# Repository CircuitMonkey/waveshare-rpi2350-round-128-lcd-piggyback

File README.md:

# waveshare-rpi2350-round-128-lcd-piggyback
Piggyback hacking PCB for the Waveshare RPi2350/2040 round 1.28 inch 240x240 LCD

Gain solder level access to the header pins on the back of this LCB module!

These are piggyback style GPIO access connector PCBs for the Waveshare 1.28 inch round LCD with RPi2350/2040 type controller.
Amazon product link example: [https://www.amazon.com/dp/B0DM1CB4YV](https://www.amazon.com/dp/B0DM1CB4YV)

If you want to try one of these boards, simply upload the PCB KiCAD design to https://oshpark.com

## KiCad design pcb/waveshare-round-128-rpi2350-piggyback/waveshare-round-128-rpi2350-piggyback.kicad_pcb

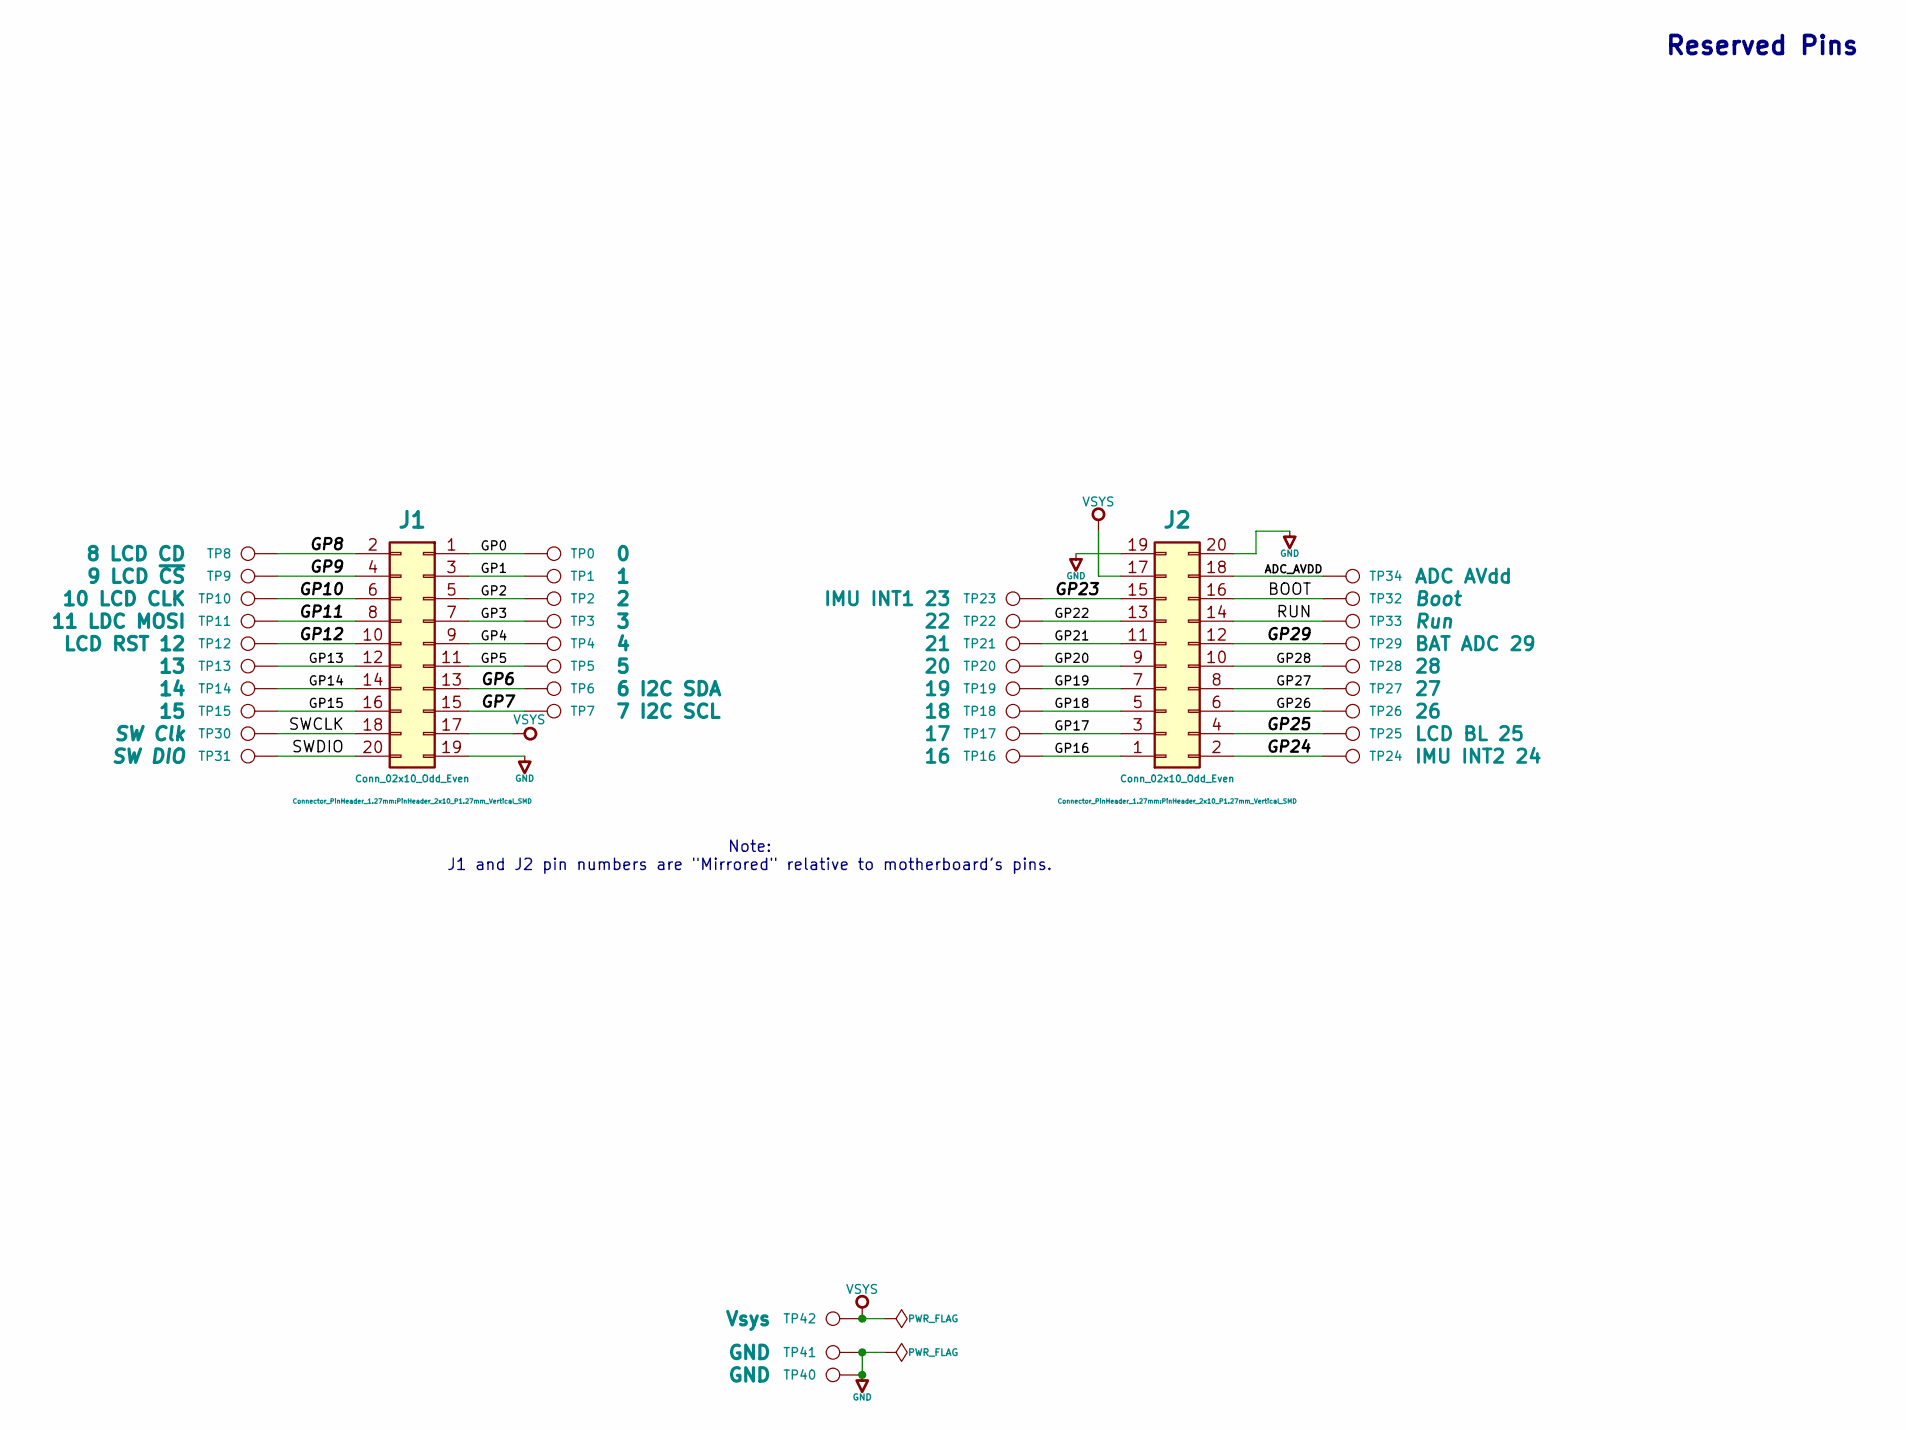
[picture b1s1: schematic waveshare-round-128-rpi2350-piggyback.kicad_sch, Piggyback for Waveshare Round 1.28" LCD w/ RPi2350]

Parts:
J1, J2: Conn_02x10_Odd_Even; PinHeader_2x10_P1.27mm_Vertical_SMD
TP0: 0; TestPoint_Pad_D2.0mm
TP1: 1; TestPoint_Pad_D2.0mm
TP2: 2; TestPoint_Pad_D2.0mm
TP3: 3; TestPoint_Pad_D2.0mm
TP4: 4; TestPoint_Pad_D2.0mm
TP5: 5; TestPoint_Pad_D2.0mm
TP6: 6 I2C SDA; TestPoint_Pad_D2.0mm
TP7: 7 I2C SCL; TestPoint_Pad_D2.0mm
TP8: 8 LCD CD; TestPoint_Pad_D2.0mm
TP9: 9 LCD ~{CS}; TestPoint_Pad_D2.0mm
TP10: 10 LCD CLK; TestPoint_Pad_D2.0mm
TP11: 11 LDC MOSI; TestPoint_Pad_D2.0mm
TP12: LCD RST 12; TestPoint_Pad_D2.0mm
TP13: 13; TestPoint_Pad_D2.0mm
TP14: 14; TestPoint_Pad_D2.0mm
TP15: 15; TestPoint_Pad_D2.0mm
TP16: 16; TestPoint_Pad_D2.0mm
TP17: 17; TestPoint_Pad_D2.0mm
TP18: 18; TestPoint_Pad_D2.0mm
TP19: 19; TestPoint_Pad_D2.0mm
TP20: 20; TestPoint_Pad_D2.0mm
TP21: 21; TestPoint_Pad_D2.0mm
TP22: 22; TestPoint_Pad_D2.0mm
TP23: IMU INT1 23; TestPoint_Pad_D2.0mm
TP24: IMU INT2 24; TestPoint_Pad_D2.0mm
TP25: LCD BL 25; TestPoint_Pad_D2.0mm
TP26: 26; TestPoint_Pad_D2.0mm
TP27: 27; TestPoint_Pad_D2.0mm
TP28: 28; TestPoint_Pad_D2.0mm
TP29: BAT ADC 29; TestPoint_Pad_D2.0mm
TP30: SW Clk; TestPoint_Pad_D2.0mm
TP31: SW DIO; TestPoint_Pad_D2.0mm
TP32: Boot; TestPoint_Pad_D2.0mm
TP33: Run; TestPoint_Pad_D2.0mm
TP34: ADC AVdd; TestPoint_Pad_D2.0mm
TP40, TP41: GND; TestPoint_Pad_D4.0mm
TP42: Vsys; TestPoint_Pad_D2.5mm

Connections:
/ADC_AVDD: J2.18, TP34.1 (1_1)
/BOOT: J2.16, TP32.1 (1_1)
/GP0: J1.1, TP0.1 (1_1)
/GP1: J1.3, TP1.1 (1_1)
/GP2: J1.5, TP2.1 (1_1)
/GP3: J1.7, TP3.1 (1_1)
/GP4: J1.9, TP4.1 (1_1)
/GP5: J1.11, TP5.1 (1_1)
/GP6: J1.13, TP6.1 (1_1)
/GP7: J1.15, TP7.1 (1_1)
/GP8: J1.2, TP8.1 (1_1)
/GP9: J1.4, TP9.1 (1_1)
/GP10: J1.6, TP10.1 (1_1)
/GP11: J1.8, TP11.1 (1_1)
/GP12: J1.10, TP12.1 (1_1)
/GP13: J1.12, TP13.1 (1_1)
/GP14: J1.14, TP14.1 (1_1)
/GP15: J1.16, TP15.1 (1_1)
/GP16: J2.1, TP16.1 (1_1)
/GP17: J2.3, TP17.1 (1_1)
/GP18: J2.5, TP18.1 (1_1)
/GP19: J2.7, TP19.1 (1_1)
/GP20: J2.9, TP20.1 (1_1)
/GP21: J2.11, TP21.1 (1_1)
/GP22: J2.13, TP22.1 (1_1)
/GP23: J2.15, TP23.1 (1_1)
/GP24: J2.2, TP24.1 (1_1)
/GP25: J2.4, TP25.1 (1_1)
/GP26: J2.6, TP26.1 (1_1)
/GP27: J2.8, TP27.1 (1_1)
/GP28: J2.10, TP28.1 (1_1)
/GP29: J2.12, TP29.1 (1_1)
/RUN: J2.14, TP33.1 (1_1)
/SWCLK: J1.18, TP30.1 (1_1)
/SWDIO: J1.20, TP31.1 (1_1)
GND: J1.19, J2.19, J2.20, TP40.1 (1_1), TP41.1 (1_1)
VSYS: J1.17, J2.17, TP42.1 (1_1)

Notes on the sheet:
Reserved Pins
Note: J1 and J2 pin numbers are "Mirrored" relative to motherboard's pins.

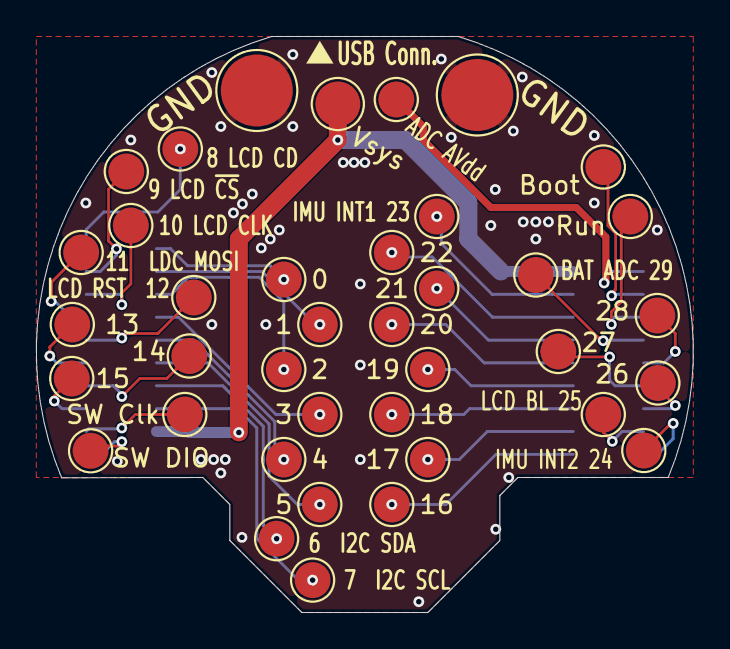
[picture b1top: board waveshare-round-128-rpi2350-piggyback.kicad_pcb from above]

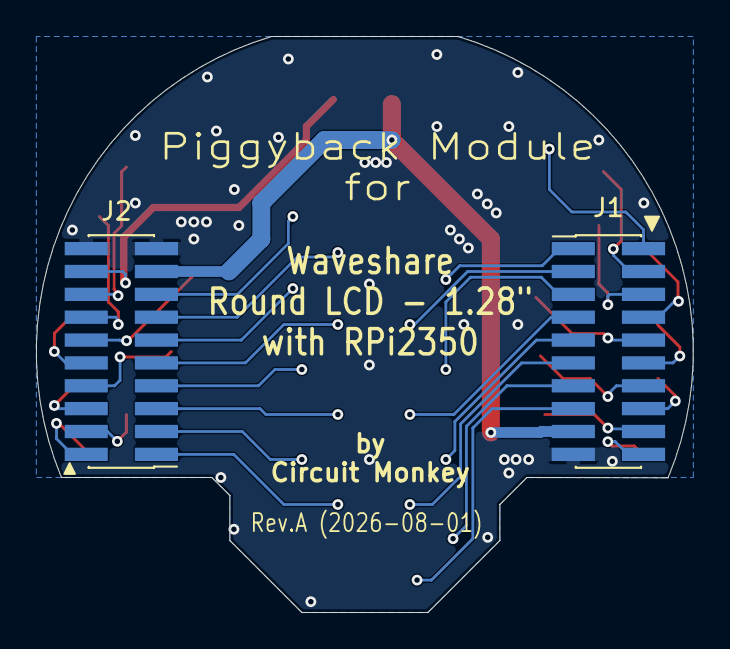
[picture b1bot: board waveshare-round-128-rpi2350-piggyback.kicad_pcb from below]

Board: 2 copper layers, 36.5 x 32.0 mm, 40 parts (2 on the bottom side), 37 nets.
